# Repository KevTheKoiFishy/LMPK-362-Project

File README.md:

# LPMK ECE 362 Final Project
#### GPS Timekeeping and Alarm with Music on RP2350

### Parts List
- RP2350 Proton Board and Debugger
- <span style="color: #777">~~DS Series RTC (I<sup>2</sup>C)~~ (Rejected)</span>
- NEO-6M GPS Module (UART) for Satellite Timekeeping
- LCD TFT Display (SPI) with SD Card Reader (SPI) for Image Storage/Display + Audio Storage
- External DAC (I2C or Custom Build with Shift-Reg) for Audio Playback
- Passive Button Array Keypad for Navigation

### Functions
- Current Time
- GPS Map
- Alarm Settings
- Stopwatch
- Timer

### Project Tasks
1. Define Objectives
    - Get GTA approval
    - Agree on design
    - Assign roles
    - Who should keep the design?
    - Agree on meeting / build times
2. High-level planning
    - Hardware Diagram
    - Software Interface Diagram
3. Detailed Hardware Design
    - Determine pin allocation via GPIO needs
    - Determine required bus speeds via part datasheets
    - Design custom peripherals (ie. DAC)
4. Hardware Prototype
    - Breadboard Build
    - Electrical Verification
5. Software Build
    - Hardware Peripheral Backends
        - Create high-level functions for controlling peripherals easily (like in `display.c`)
        - A way to communicate with frontend
    - Application Frontend
        - Interface and Transition Logic
        - Graphics and UX Design
6. Iterate and Debug
7. PCB Build (if time available)
8. Report / Presentations

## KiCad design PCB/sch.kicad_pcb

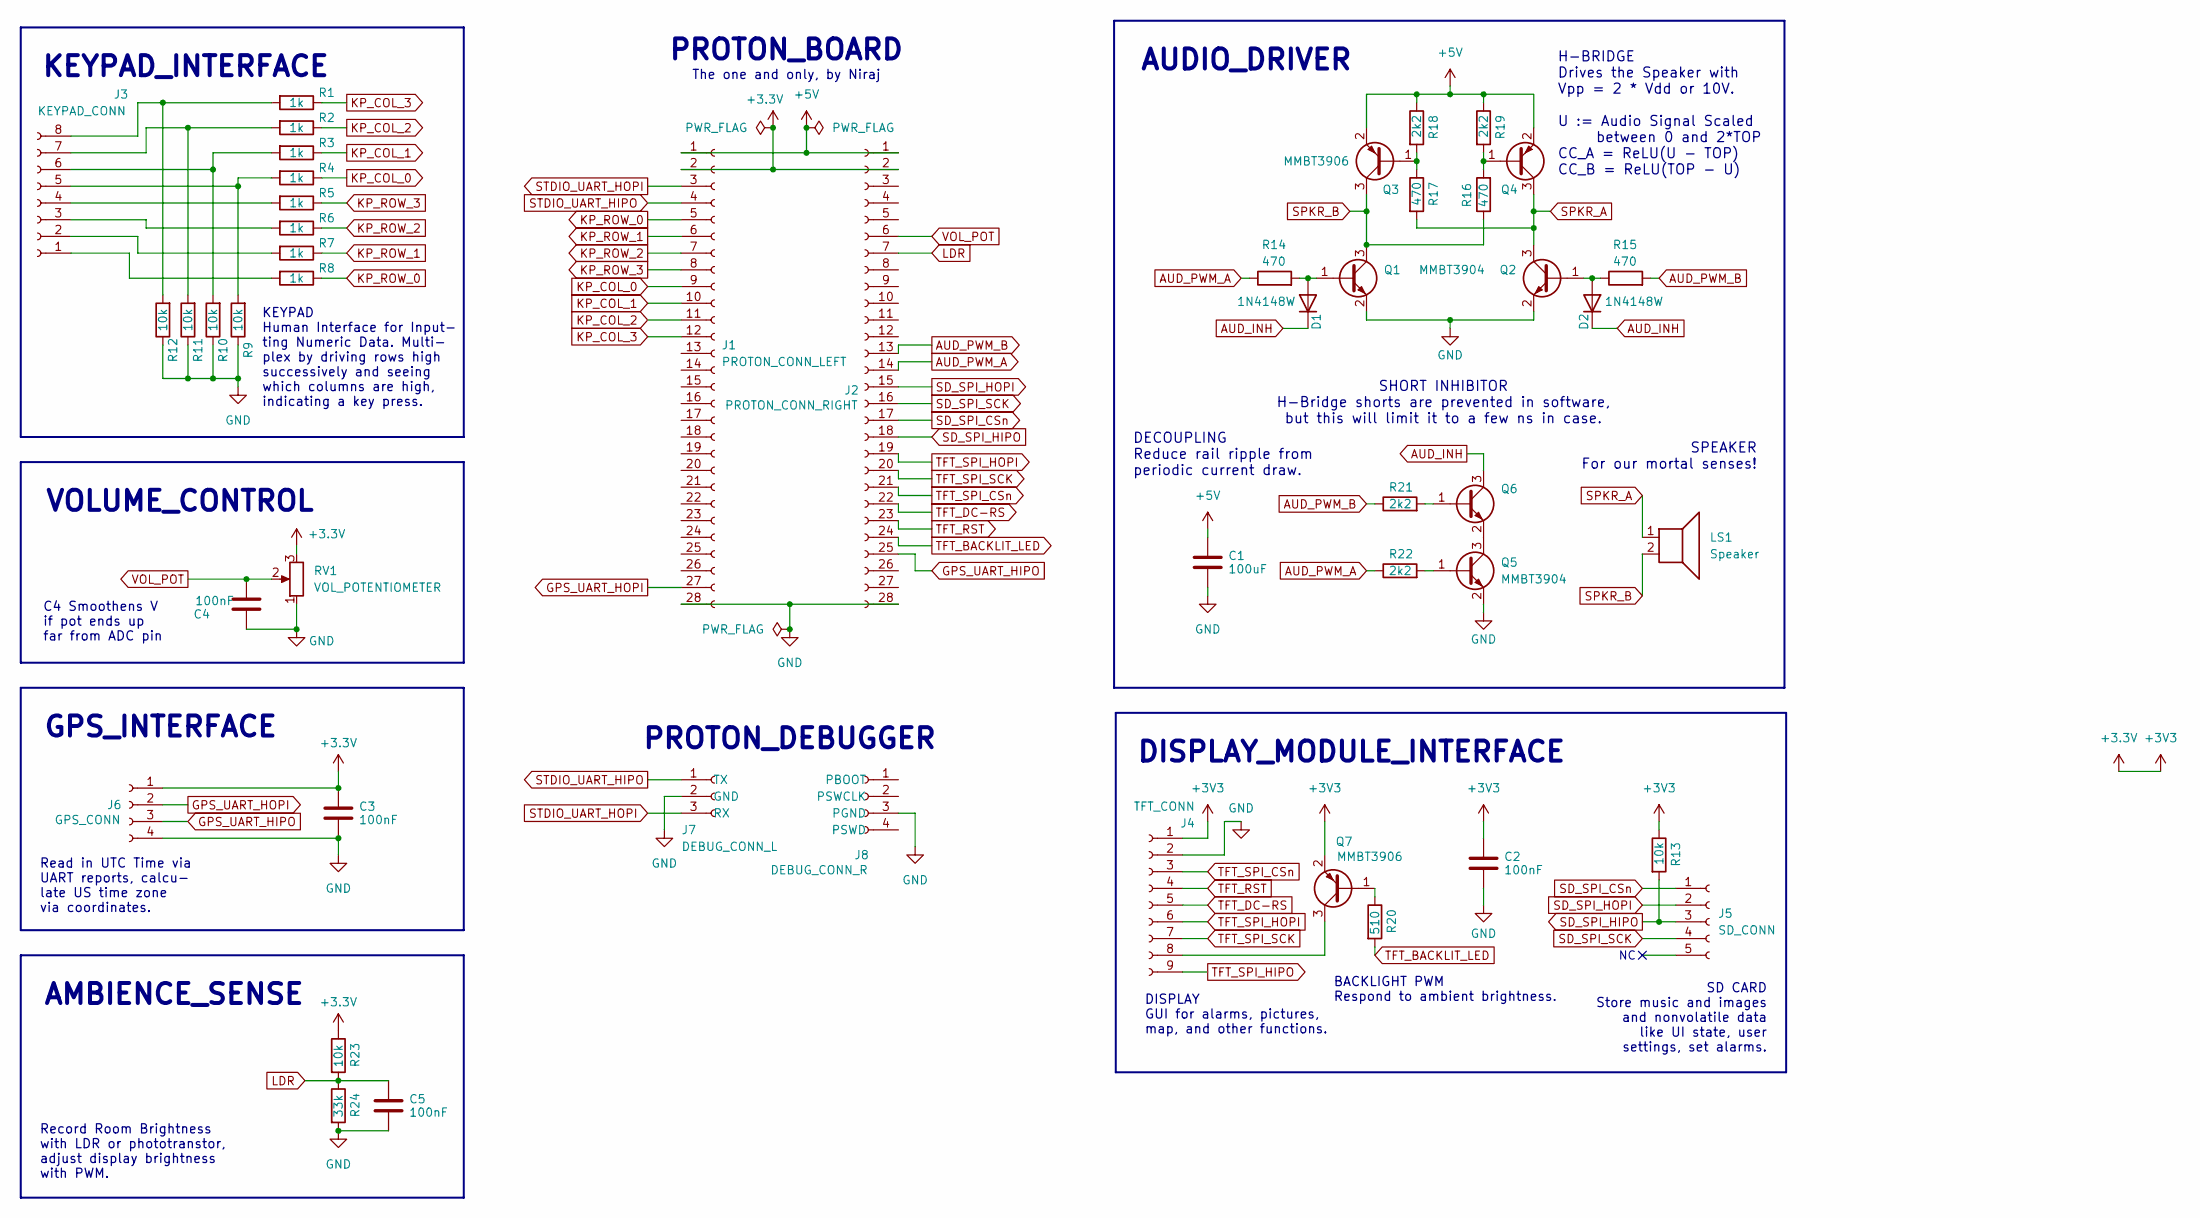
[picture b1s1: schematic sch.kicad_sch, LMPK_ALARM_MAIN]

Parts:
C1: 100uF; CP_Radial_D8.0mm_P2.50mm; LCSC C109392
C2, C3, C4, C5: 100nF; C_0201_0603Metric_Pad0.64x0.40mm; LCSC C14663
D1, D2: 1N4148W; D_SOD-123; LCSC C917030
J1: PROTON_CONN_LEFT; PinSocket_1x28_P2.54mm_Vertical
J2: PROTON_CONN_RIGHT; PinSocket_1x28_P2.54mm_Vertical
J3: KEYPAD_CONN; PinSocket_1x08_P2.54mm_Vertical
J4: TFT_CONN; PinSocket_1x09_P2.54mm_Vertical
J5: SD_CONN; PinSocket_1x05_P2.54mm_Vertical
J6: GPS_CONN; PinSocket_1x04_P2.54mm_Vertical
J7: DEBUG_CONN_L; PinSocket_1x03_P2.54mm_Vertical
J8: DEBUG_CONN_R; PinSocket_1x04_P2.54mm_Vertical
LS1: Speaker; CONN_2PIN_SCREW
Q1, Q2, Q5, Q6: MMBT3904; SOT-23; LCSC C81464
Q3, Q4, Q7: MMBT3906; SOT-23; LCSC C53444
R1, R2, R3, R4, R5, R6, R7, R8: 1k; R_0201_0603Metric_Pad0.64x0.40mm; LCSC C2907002
R9, R10, R11, R12, R13: 10k; R_0201_0603Metric_Pad0.64x0.40mm; LCSC C2906982
R14, R15, R16, R17: 470; R_0201_0603Metric_Pad0.64x0.40mm; LCSC C23179
R18, R19, R21, R22: 2k2; R_0201_0603Metric_Pad0.64x0.40mm; LCSC C2907117
R20: 510; R_0201_0603Metric_Pad0.64x0.40mm; LCSC C2907048
R23: 10k; R_LDR_5.1x4.3mm_P3.4mm_Vertical; LCSC C125629
R24: 33k; R_0201_0603Metric_Pad0.64x0.40mm; LCSC C2907028
RV1: VOL_POTENTIOMETER; CONN_3PIN_SCREW

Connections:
+3.3V: C2.1, C3.1, J1.2, J2.2, J4.1, J6.1, Q7.2 (E), R13.1, R23.1, RV1.3
+5V: C1.1, J1.1, J2.1, Q3.2 (E), Q4.2 (E), R18.1, R19.1
AUD_INH: D1.1 (K), D2.1 (K), Q6.3 (C)
AUD_PWM_A: J2.14, R14.1, R22.1
AUD_PWM_B: J2.13, R15.2, R21.1
GND: C1.2, C2.2, C3.2, C4.1, C5.2, J1.28, J2.28, J4.2, J6.4, J7.2 (GND), J8.3 (PGND), Q1.2 (E), Q2.2 (E), Q5.2 (E), R9.1, R10.1, R11.1, R12.1, R24.2, RV1.1
GPS_UART_HIPO: J2.25, J6.3
GPS_UART_HOPI: J1.27, J6.2
KP_COL_0: J1.9, R4.1
KP_COL_1: J1.10, R3.1
KP_COL_2: J1.11, R2.1
KP_COL_3: J1.12, R1.1
KP_ROW_0: J1.5, R8.1
KP_ROW_1: J1.6, R7.1
KP_ROW_2: J1.7, R6.1
KP_ROW_3: J1.8, R5.1
LDR: C5.1, J2.7, R23.2, R24.1
unnamed: D1.2 (A), Q1.1 (B), R14.2
unnamed: D2.2 (A), Q2.1 (B), R15.1
unnamed: J3.1, R8.2
unnamed: J3.2, R7.2
unnamed: J3.3, R6.2
unnamed: J3.4, R5.2
unnamed: J3.5, R4.2, R9.2
unnamed: J3.6, R3.2, R10.2
unnamed: J3.7, R2.2, R11.2
unnamed: J3.8, R1.2, R12.2
unnamed: J4.8, Q7.3 (C)
unnamed: Q3.1 (B), R17.1, R18.2
unnamed: Q4.1 (B), R16.2, R19.2
unnamed: Q5.1 (B), R22.2
unnamed: Q5.3 (C), Q6.2 (E)
unnamed: Q6.1 (B), R21.2
unnamed: Q7.1 (B), R20.1
SD_SPI_CSn: J2.17, J5.1
SD_SPI_HIPO: J2.18, J5.3, R13.2
SD_SPI_HOPI: J2.15, J5.2
SD_SPI_SCK: J2.16, J5.4
SPKR_A: LS1.1, Q2.3 (C), Q4.3 (C), R17.2
SPKR_B: LS1.2, Q1.3 (C), Q3.3 (C), R16.1
STDIO_UART_HIPO: J1.4, J7.1 (TX)
STDIO_UART_HOPI: J1.3, J7.3 (RX)
TFT_BACKLIT_LED: J2.24, R20.2
TFT_DC-RS: J2.22, J4.5
TFT_RST: J2.23, J4.4
TFT_SPI_CSn: J2.21, J4.3
TFT_SPI_HIPO: J4.9
TFT_SPI_HOPI: J2.19, J4.6
TFT_SPI_SCK: J2.20, J4.7
VOL_POT: C4.2, J2.6, RV1.2

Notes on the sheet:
C4 Smoothens V if pot ends up far from ADC pin
The one and only, by Niraj
BACKLIGHT PWM Respond to ambient brightness.
AMBIENCE_SENSE
KEYPAD_INTERFACE
DISPLAY_MODULE_INTERFACE
VOLUME_CONTROL
H-BRIDGE Drives the Speaker with Vpp = 2 * Vdd or 10V. U := Audio Signal Scaled between 0 and 2*TOP CC_A = ReLU(U - TOP) CC_B = ReLU(TOP - U)
PROTON_DEBUGGER
KEYPAD Human Interface for Input- ting Numeric Data. Multi- plex by driving rows high successively and seeing which columns are high, indicating a key press.
SHORT INHIBITOR H-Bridge shorts are prevented in software, but this will limit it to a few ns in case.
DISPLAY GUI for alarms, pictures, map, and other functions.
AUDIO_DRIVER
GPS_INTERFACE
Read in UTC Time via UART reports, calcu- late US time zone via coordinates.
SD CARD Store music and images and nonvolatile data like UI state, user settings, set alarms.
PROTON_BOARD
DECOUPLING Reduce rail ripple from periodic current draw.
Record Room Brightness with LDR or phototranstor, adjust display brightness with PWM.
SPEAKER For our mortal senses!

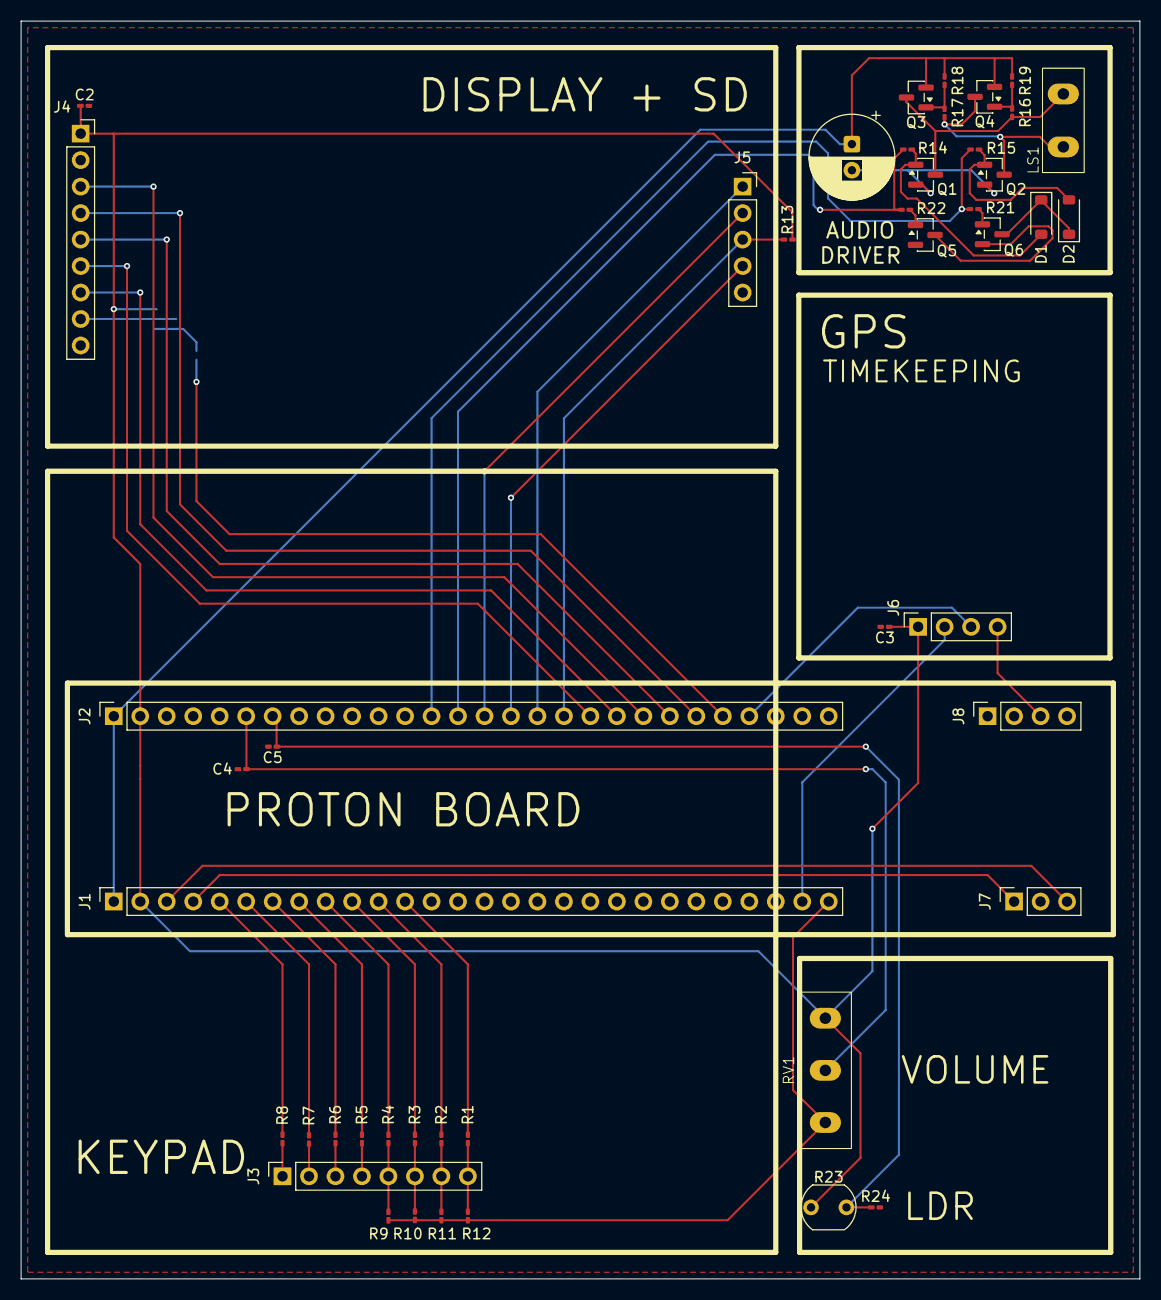
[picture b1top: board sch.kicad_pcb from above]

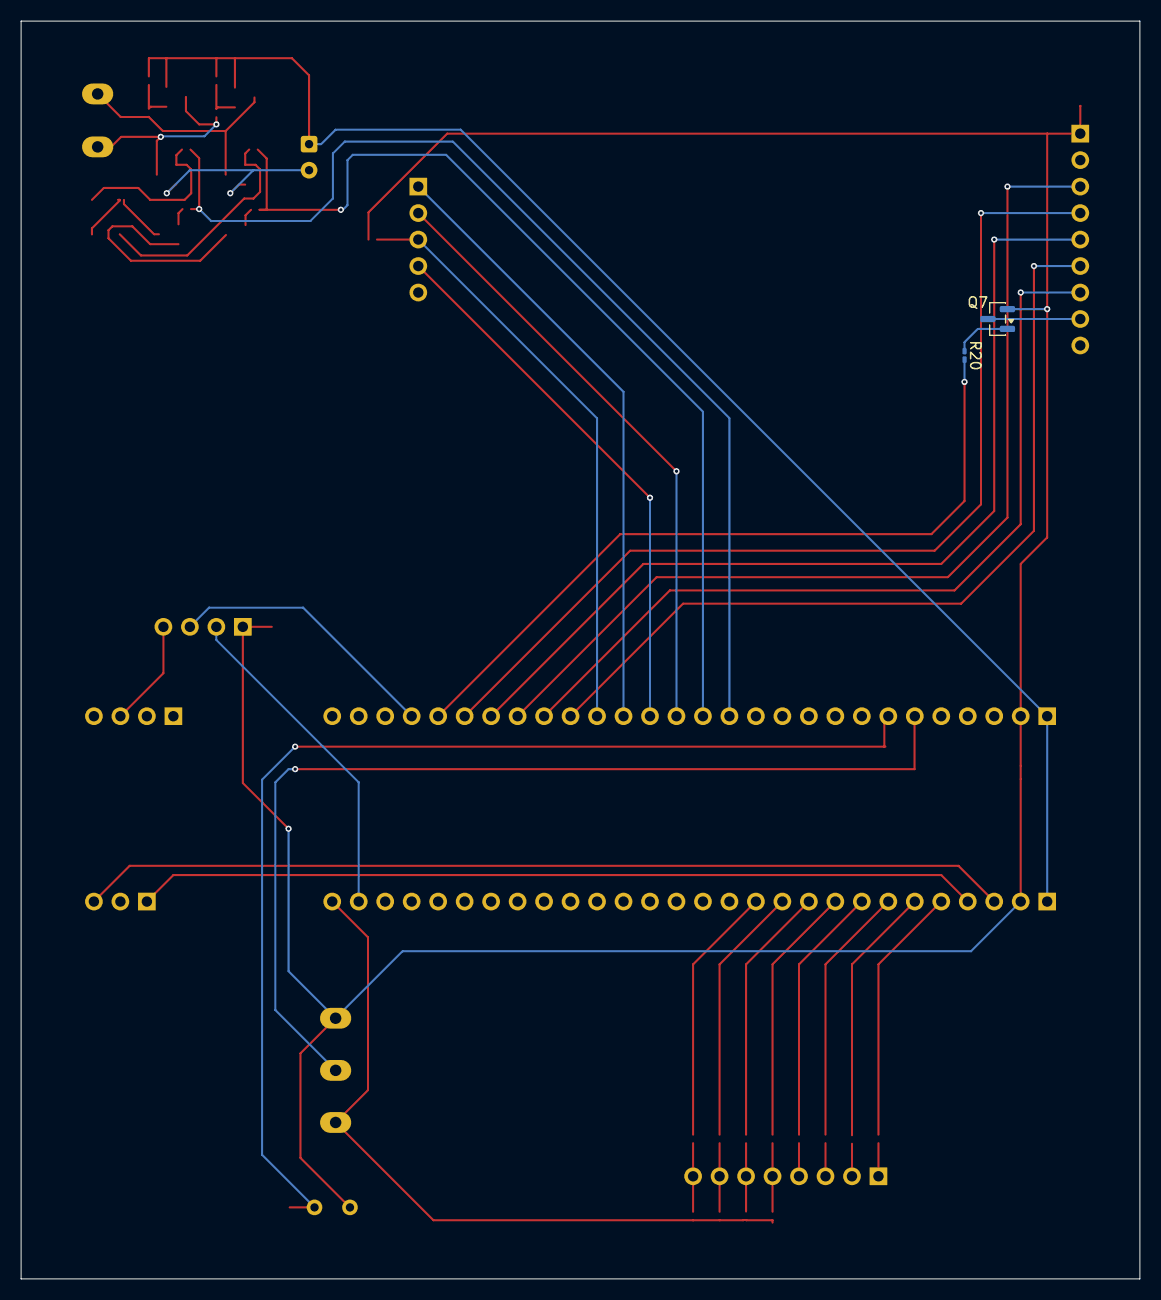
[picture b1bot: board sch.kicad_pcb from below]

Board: 2 copper layers, 107.3 x 120.7 mm, 48 parts (2 on the bottom side), 49 nets.

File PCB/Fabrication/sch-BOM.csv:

Comment,Designator,Footprint,LCSC
"100nF","C2,C3,C4,C5","Capacitor_SMD:C_0201_0603Metric_Pad0.64x0.40mm","C14663"
"1N4148W","D1,D2","Diode_SMD:D_SOD-123","C917030"
"PROTON_CONN_LEFT","J1","Connector_PinSocket_2.54mm:PinSocket_1x28_P2.54mm_Vertical",""
"PROTON_CONN_RIGHT","J2","Connector_PinSocket_2.54mm:PinSocket_1x28_P2.54mm_Vertical",""
"KEYPAD_CONN","J3","Connector_PinSocket_2.54mm:PinSocket_1x08_P2.54mm_Vertical",""
"TFT_CONN","J4","Connector_PinSocket_2.54mm:PinSocket_1x09_P2.54mm_Vertical",""
"SD_CONN","J5","Connector_PinSocket_2.54mm:PinSocket_1x05_P2.54mm_Vertical",""
"GPS_CONN","J6","Connector_PinSocket_2.54mm:PinSocket_1x04_P2.54mm_Vertical",""
"DEBUG_CONN_L","J7","Connector_PinSocket_2.54mm:PinSocket_1x03_P2.54mm_Vertical",""
"DEBUG_CONN_R","J8","Connector_PinSocket_2.54mm:PinSocket_1x04_P2.54mm_Vertical",""
"MMBT3904","Q1,Q2,Q5,Q6","Package_TO_SOT_SMD:SOT-23","C81464"
"MMBT3906","Q3,Q4,Q7","Package_TO_SOT_SMD:SOT-23","C53444"
"1k","R1,R2,R3,R4,R5,R6,R7,R8","Resistor_SMD:R_0201_0603Metric_Pad0.64x0.40mm","C2907002"
"470","R14,R15,R16,R17","Resistor_SMD:R_0201_0603Metric_Pad0.64x0.40mm","C23179"
"2k2","R18,R19,R21,R22","Resistor_SMD:R_0201_0603Metric_Pad0.64x0.40mm","C2907117"
"510","R20","Resistor_SMD:R_0201_0603Metric_Pad0.64x0.40mm","C2907048"
"33k","R24","Resistor_SMD:R_0201_0603Metric_Pad0.64x0.40mm","C2907028"
"10k","R9,R10,R11,R12,R13","Resistor_SMD:R_0201_0603Metric_Pad0.64x0.40mm","C2906982"

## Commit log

2025-10-08 Some things to start with
2025-10-08 Updated Gitignore
2025-11-04 💾 SD Card SPI functions, Audio Buffer
2025-11-04 🧹 Clean up a bit
2025-11-12 gps and timezone functions
2025-11-19 🔉 Class D Speaker Driver Circuit
2025-11-19 💾 SD Card Works!
2025-11-19 🕵🏻‍♀️ SD Parse Audio Headers
2025-11-20 🍪 Decide Pin Assignments
2025-11-20 PCB Started
2025-11-21 SCH Done
2025-11-21 PCB Done
2025-11-21 Amended with LDR, Added Gerbers, BOM, positions
2025-11-22 🔊 Audio works but ISR takes longer than its trigger period
2025-11-22 🔊 Slight Improvement by Cutting out Buffer
2025-11-23 🔊 Multicore approach, race condition nightmare 😭😭😭
2025-11-23 🔊 Real time playing, sometimes sd access drops
2025-11-23 🔊 Only minor glitches after replacing write-to-read-ptr with write-entire-buff-when-almost-empty
2025-11-23 🔊 Try double buffer, similar issue
2025-11-23 🔊 Okay fr this is probably good enough
2025-11-25 🔊 SD Audio Docs
2025-11-25 ⏰ GPS Time Parsing
2025-11-26 🔊 SD Close and Reopen File Works
2025-12-01 control in progress
2025-12-02 ⏰ Add some funcs for gps time
2025-12-02 🔊 Integrate volume control and sd_audio functions; resolve code errors; temporarily remove 7seg output to reduce runtime
2025-12-02 🕹️ control audio and visual
2025-12-02 🕹️ control audio/visual
2025-12-03 TFT display
2025-12-03 🔊 Untested Volume Ramp Integration
2025-12-03 📝 ambience_control: Rename for Merging
2025-12-04 🔊 Untested Volume Ramp and Pushbutton Control Integration
2025-12-04 🔊 Untested Adaptive Brightness Control
2025-12-04 tft display main
2025-12-05 🔁 Integrate all except display so far
2025-12-05 😴 TESTED Ambience Control Integration
2025-12-05 😴 TESTED GPS Time and Alarm Fire Integration. TIMER HANDLER CONFLICT NIGHTMARE UGHGHHGHGHGH
2025-12-05 😴 TESTED Display and Keypad Integration
2025-12-05 😴 TESTED Adaptive Brightness Control Integration
